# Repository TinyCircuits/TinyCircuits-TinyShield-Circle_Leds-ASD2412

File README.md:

# TinyCircuits TinyShield Circle Edge LEDs
# ASD2412 Rev1

The design files are located under design_files/ for the TinyCircuits ASD2412 Rev 1 PCB.  This is a Tiny shield board (Square Version, 20mm x 20mm, or Circular 20mm diameter) that has a 21 LEDs around the border.

Format is in Cadsoft Eagle format - Eagle version 6.2 was used for the original design.

For more infomation on this, check out the product page at TinyCircuits.com: https://tinycircuits.com/collections/leds-displays/products/circle-edge-led-tinyshield

# License:

Design by TinyCircuits.
All design files are released under the Creative Commons Attribution Share-Alike 3.0 License, see the following link for details: http://creativecommons.org/licenses/by-sa/3.0

All text above must be included in any redistribution or derived design

This project uses designs and concepts developed as part of the Arduino project and the LilyPad project.  The TinyCircuits design files themselves (schematics, PCB and libraries) are not directly derived from these works' design files and have been created new, however the concepts and basic architecture behind the TinyDuino and TinyLily products are derived and we thank the hard work of the organizations below for their contributions to open-source hardware:
  
Original Arduino Uno Design by Team Arduino

LilyPad Arduino Design by Leah Buechley and Sparkfun Electronics

Please support the open-source hardware community

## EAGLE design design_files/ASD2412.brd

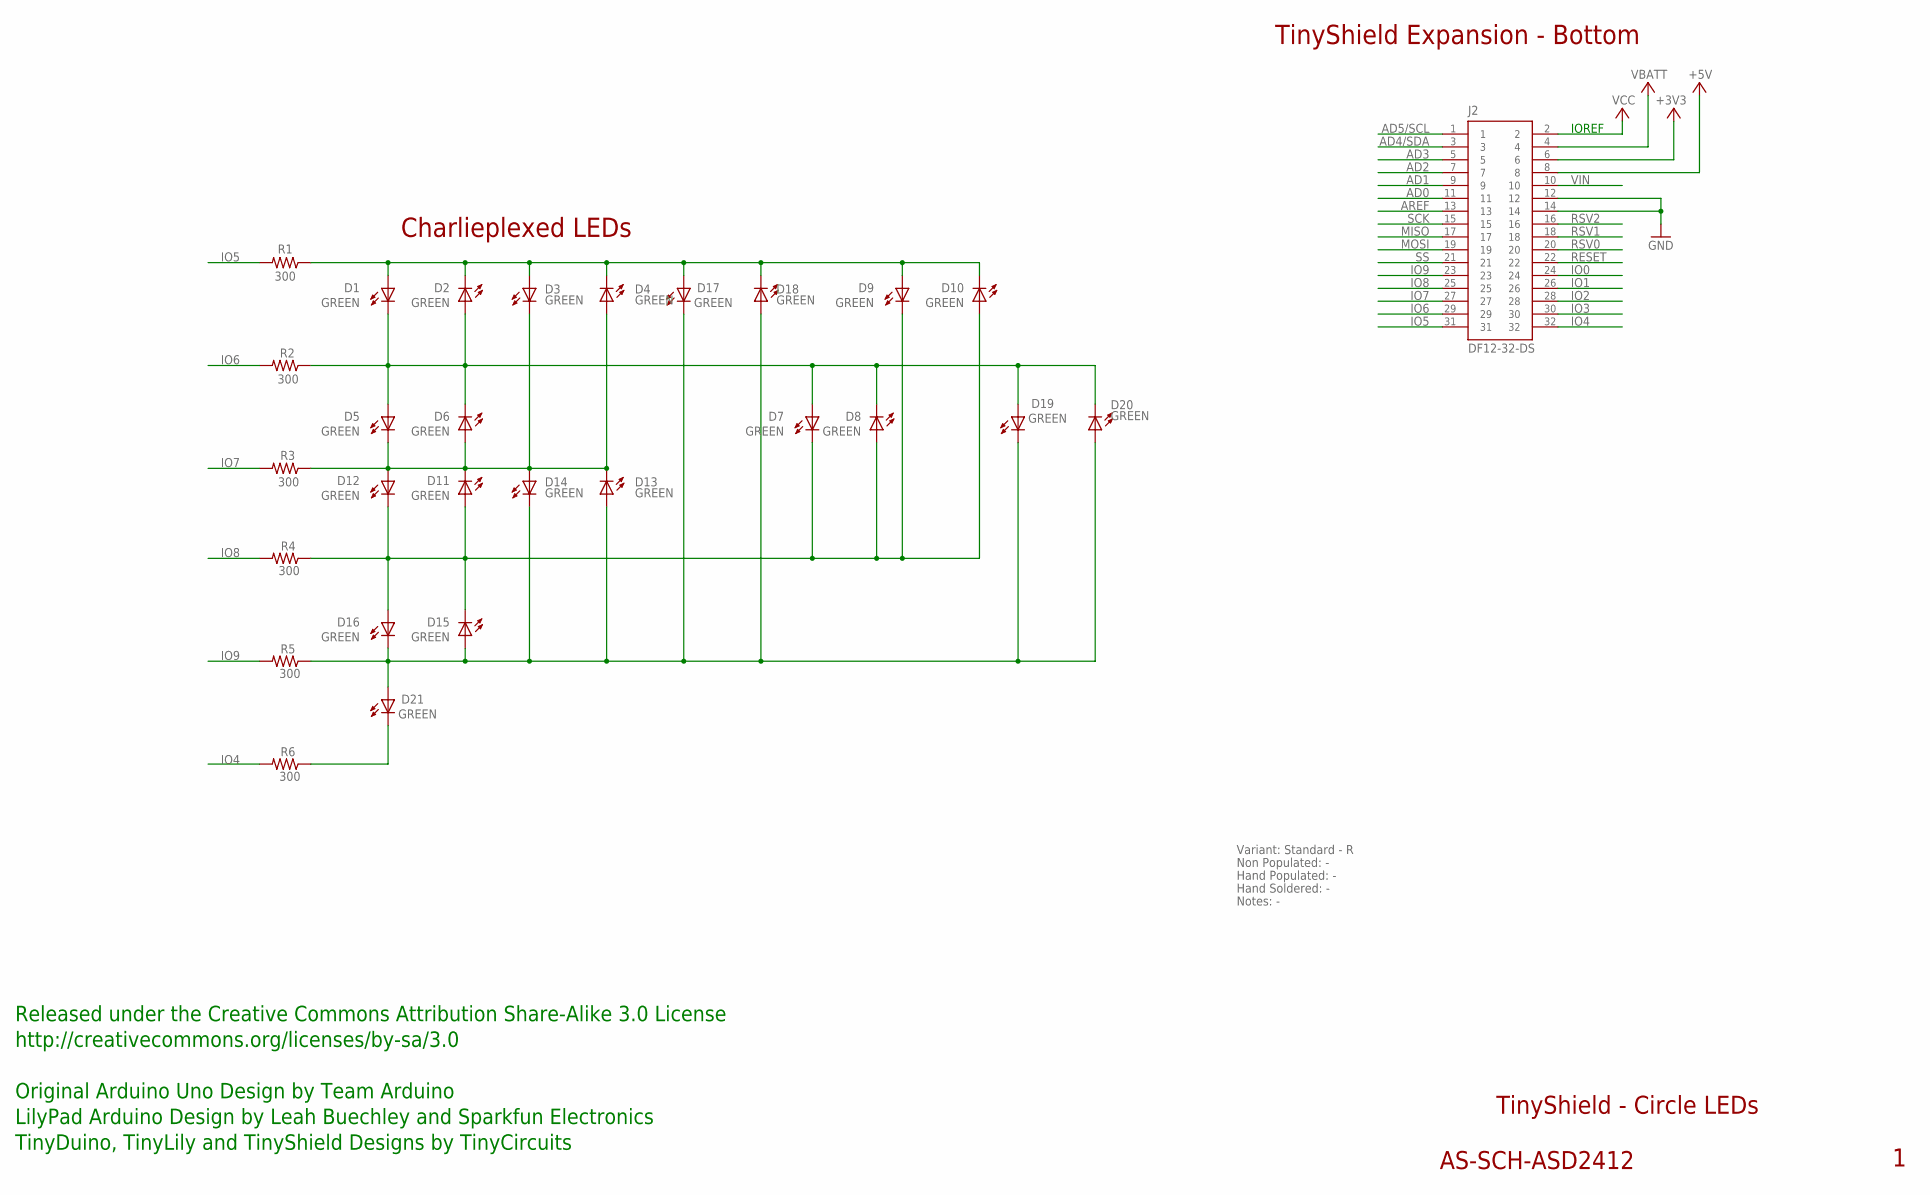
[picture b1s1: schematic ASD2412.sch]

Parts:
D1, D2, D3, D4, D5, D6, D7, D8, D9, D10, D11, D12, D13, D14, D15, D16: GREEN; LNJ_LED; PARTNO AS-ITM-00011
D17, D18, D19, D20, D21: GREEN; LNJ_LED
J2: DF12-32-DS; PARTNO AS-ITM-00012
R1, R6: 300; 0402; PARTNO AS-ITM-00016
R2, R3, R4, R5: 300; 0402

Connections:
+3V3: J2.6
+5V: J2.8
AD0: J2.11
AD1: J2.9
AD2: J2.7
AD3: J2.5
AD4/SDA: J2.3
AD5/SCL: J2.1
AREF: J2.13
GND: J2.12, J2.14
IO0: J2.24
IO1: J2.26
IO2: J2.28
IO3: J2.30
IO4: J2.32, R6.2
IO5: J2.31, R1.2
IO6: J2.29, R2.2
IO7: J2.27, R3.2
IO8: J2.25, R4.2
IO9: J2.23, R5.2
MISO: J2.17
MOSI: J2.19
unnamed: D1.C, D2.A, D5.A, D6.C, D7.A, D8.C, D19.A, D20.C, R2.1
unnamed: D21.C, R6.1
unnamed: D1.A, D2.C, D3.A, D4.C, D9.A, D10.C, D17.A, D18.C, R1.1
unnamed: D3.C, D4.A, D5.C, D6.A, D11.C, D12.A, D13.C, D14.A, R3.1
unnamed: D7.C, D8.A, D9.C, D10.A, D11.A, D12.C, D15.C, D16.A, R4.1
unnamed: D13.A, D14.C, D15.A, D16.C, D17.C, D18.A, D19.C, D20.A, D21.A, R5.1
RESET: J2.22
RSV0: J2.20
RSV1: J2.18
RSV2: J2.16
SCK: J2.15
SS: J2.21
VBATT: J2.4
VCC: J2.2
VIN: J2.10

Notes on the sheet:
TinyShield Expansion - Bottom
Charlieplexed LEDs
TinyShield - Circle LEDs
AS-SCH-ASD2412
IOREF
Released under the Creative Commons Attribution Share-Alike 3.0 License
http://creativecommons.org/licenses/by-sa/3.0
LilyPad Arduino Design by Leah Buechley and Sparkfun Electronics
TinyDuino, TinyLily and TinyShield Designs by TinyCircuits
Original Arduino Uno Design by Team Arduino
Non Populated: -
Hand Populated: -
Hand Soldered: -
Variant: Standard - R
Notes: -

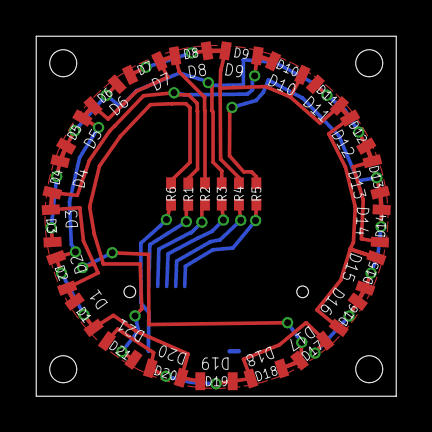
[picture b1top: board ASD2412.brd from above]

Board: 2 copper layers, 20.0 x 20.0 mm, 29 parts (1 on the bottom side), 13 nets.

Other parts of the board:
U$1: DOCFIELD-TINYCIRCUITS-PCB

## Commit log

2014-08-24 Updated Link
2019-01-04 Update format
2019-01-07 updated comments
2019-01-11 added tutorial images
2019-01-11 added .zip files
2019-01-11 updated images
2019-05-20 changed naming
2020-02-11 image update
2020-07-28 Add CAD data
2020-08-14 Update CAD drawing
